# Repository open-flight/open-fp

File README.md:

# open-fp

Open source force plates for golf performance.

Two low-profile golf force plates, one per foot. Each plate has four load cells, eight in total. A single Arduino UNO Q reads them, and a web dashboard on the LAN shows live weight shift and swing replay.

> **Status:** Hardware bring-up is under way. Four of the eight load cells read on one SPI bus through the toe stripboard carrier, at about 944 Hz each (`bench/ads1220_all`; results in [`docs/VERIFIED.md`](docs/VERIFIED.md)). An assembled, no-solder ADC board for all eight channels has been designed and ordered ([`hardware/pcb/adc-board`](hardware/pcb/adc-board/README.md)). The pure-Python processing (`app/python/open_fp/`: protocol, clock, pipeline, calibration, swing detection, storage) is written and tested, and runs under `pytest` with no hardware. The web UI and a desktop simulator work too: run `python tools/sim/sim_server.py` and open http://localhost:7070 to see live weight shift, swing capture, replay and diagnostics on synthetic swings. **Not written yet:** the production MCU firmware (`app/sketch/`) and the board-side `main.py` that links it to the pipeline. Milestones: [`docs/PROJECT_INIT.md` §12](docs/PROJECT_INIT.md#12-milestones-and-acceptance-checks) (M0–M1 done, M2 in progress).

## What it measures

| Output | Notes |
|---|---|
| Vertical force per foot (Fz) | N and %BW |
| Centre of pressure (CoP) per foot and combined | mm, in the stance frame |
| Lead/trail weight % | set by handedness (RH/LH) |
| Swing capture and metrics | address, max trail, transition, max lead, finish |

## Limitations

- **Vertical force only.** Each plate has four vertical cells, which give Fz and CoP (x, y) per plate. The plates cannot measure shear (horizontal) forces or torque about the vertical axis, so the app does not report ground torque or horizontal force.
- **Inter-channel skew up to ~1 ms.** Each ADC runs on its own oscillator. All eight are read on the DRDY signal of one board.
- **200 Hz stream.** The MCU↔Linux router link runs at 115200 baud. That is enough for weight shift but too slow for impact transients.
- **Temperature drift.** Half-bridge cells and their completion resistors drift with temperature. The app auto-zeros when the plates are empty.
- **Impact timing is external.** Impact is known only when the OpenFlight launch monitor sends a shot event or you mark it by hand. Over Wi-Fi with NTP, expect 5–20 ms of error.

## Hardware

- 2 × 12" × 12" × 1/4" 6061 aluminum plates, 8 × 50 kg half-bridge load cells, 8 × ADS1220 24-bit ADCs, 1 × Arduino UNO Q
- Bill of materials: [`hardware/bom.md`](hardware/bom.md) (its Buy column uses Amazon affiliate links)
- ADC wiring: hand-built stripboard carriers ([`docs/harness.md`](docs/harness.md)), or the assembled, no-solder ADC board in [`hardware/pcb/adc-board/`](hardware/pcb/adc-board/README.md)
- Print files: [`hardware/cad/`](hardware/cad/) (STL, STEP, and the CadQuery sources)
- Assembly: [`docs/assembly.md`](docs/assembly.md) · Wiring: [`docs/wiring.md`](docs/wiring.md) · System wiring, step by step: [`docs/harness.md`](docs/harness.md) · One-cell bench test: [`docs/bench-single-cell.md`](docs/bench-single-cell.md) · Calibration: [`docs/calibration.md`](docs/calibration.md)

## Repository layout

```
app/        Arduino App Lab app: MCU sketch, Python processing, static web UI
bench/      bring-up sketches for the ADS1220s
docs/       project spec, assembly, wiring, calibration, VERIFIED log
hardware/   BOM and CAD (STL/STEP in Git LFS)
tools/      deploy scripts, desktop simulator, offline analysis
tests/      pytest suite, runs without hardware
```

## Setup

Full walkthrough from a fresh clone and an unboxed board: **[`docs/SETUP.md`](docs/SETUP.md)**. The short version:

```bash
tools/dev_setup.sh          # dev machine: git-lfs, arduino-cli + UNO Q core, CAD files, .venv
# App Lab: first-boot the board as "open-fp", then create app "open-fp" with the WebUI - HTML brick
tools/board_setup.sh        # install your SSH key on the board
tools/deploy.sh             # push app/ and restart; UI at http://open-fp.local:7000
tools/logs.sh               # follow the app's Python logs
```

## Contributing

Build reports, fixes and new features are welcome. Start with [`CONTRIBUTING.md`](CONTRIBUTING.md): it covers the dev setup (no hardware needed), the checks CI runs, and how hardware changes are recorded. Please follow the [Code of Conduct](CODE_OF_CONDUCT.md), and report security issues privately as described in [`SECURITY.md`](SECURITY.md).

## License

[AGPL-3.0](LICENSE), the same license as [OpenFlight](https://github.com/open-flight/openflight).

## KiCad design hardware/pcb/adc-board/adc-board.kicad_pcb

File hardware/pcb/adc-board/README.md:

# ADC board (8 × ADS1220, UNO Q shield)

One assembled PCB that replaces the two stripboard ADC carriers, the eight ADS1220 breakouts, the bridge resistors and the whole wire harness. It plugs straight onto the UNO Q like any UNO shield. Each load-cell cable plugs into its own JST-XH socket. PCBWay assembles every part, so you don't solder anything.

**Rev B** (this revision) is the same circuit as rev A in a shorter board: 204.5 mm instead of 284 mm, with an OpenFlight logo on the top silkscreen. The parts, nets, pin map and each channel's layout are unchanged; only where the channels sit along the board moved. Rev A was built and passed bring-up (all 8 ADCs read back, supply and reference checked) on 2026-11-09. The enclosure in `hardware/cad` is now rev B to match (see below).

**Firmware doesn't change.** The pin map and the ADC configuration (`0E C4 40 00`: AIN0−AIN1, gain 128, PGA on, 1 kSPS turbo, continuous, external reference REFP0/REFN0) are the same as on the stripboard build.

| | |
|---|---|
| Board | 204.5 × 50 mm (54.7 mm at the header tabs), 2 layers, 1.6 mm FR4, 1 oz |
| Parts | 8 × ADS1220IPWR (on the board itself, not modules), 8 × JST-XH 3-pin side-entry SMT, 4 SMD shield headers, 0603/0805 passives. **All on the underside.** The top has copper and silkscreen only |
| Renders | [`renders/`](renders): top, bottom, 3D |
| Schematic | [`adc-board-schematic.pdf`](adc-board-schematic.pdf) |
| Order files | [`adc-board-gerbers.zip`](adc-board-gerbers.zip), [`assembly/adc-board-bom.csv`](assembly/adc-board-bom.csv), [`assembly/adc-board-centroid.csv`](assembly/adc-board-centroid.csv) |
| Checks | ERC 0 errors 0 warnings; DRC 0 errors **and 0 warnings**, 0 unconnected, schematic parity clean (`kicad-cli`, KiCad 10.0.4). Against rev A: same 115 footprints, every pad on the same net, every channel's parts at the same offsets and rotations from its JST, shield headers at the same UNO Q positions, BOM byte-identical, 16 keepouts. Gerbers re-read: outline 204.50 × 54.70 mm, 187 plated and 4 mounting holes |

## Circuit (one channel; there are eight)

The same circuit as the proven breakout build, with the chip on the board:

- **ADS1220IPWR** (TSSOP-16). AVDD and DVDD go to 3V3, AVSS and DGND to GND. A 100 nF X7R sits at each supply pin, plus 10 µF per channel.
- **Ratiometric reference:** REFP0 goes to 3V3 (the same rail as the cell's E+) and REFN0 to GND, with 100 nF across them at the pins.
- **CLK** goes to GND (internal oscillator). AIN2 and AIN3 are not connected.
- **AIN0 = cell S.** **AIN1** is the midpoint of a 1.5 kΩ / 1.5 kΩ divider (Susumu RG1608P, 0.1 %, 25 ppm/°C thin film, 0603). The two resistors sit side by side next to their ADC, so they share its temperature. AIN1 is about 1.65 V, the same as the stripboard's 1 kΩ pair. Each channel draws about 3.3 mA in total (cell 1.65 mA, divider 1.1 mA, ADC ~0.4 mA), so the whole board draws about 30 mA from the Q's 3V3 pin.
- **Input RC filter (new):** 100 Ω in series with AIN0 and AIN1, 10 nF C0G across them, 1 nF C0G from each to GND. That's a differential corner of about 76 kHz and a common-mode corner of about 1.6 MHz. It keeps RF and SPI edges out of the PGA without touching the 1 kSPS signal.
- **JST-XH 3-pin** per channel. **Pin 1 = E+ (white), pin 2 = E− (black), pin 3 = S (red)**, the same order as the cradle-end JST in [`docs/wiring.md` §3–4](../../../docs/wiring.md#3-put-jst-xh-plugs-on-the-cells). The silkscreen shows the channel name, pin 1 and W/B/R next to every socket, on both sides.
- **Shared SPI.** SCLK, DIN and DOUT/DRDY go to all eight chips; SCLK has a 33 Ω series resistor at the Q. Only **L1's DRDY pin goes to D2**. The other seven DRDY pins are left unconnected (they are push-pull outputs and must never be joined). DOUT goes high-Z while CS is high, so all eight share MISO.
- **3V3 entry:** 10 µF + 100 nF next to the header's 3V3 pin. There's no power LED.

### UNO Q pin map (unchanged)

| Q pin | Net | | Q pin | Net |
|---|---|---|---|---|
| D3 | CS L1 | | D13 | SCLK (via R1 33 Ω) |
| D4 | CS L2 | | D11 | MOSI → DIN |
| D5 | CS L3 | | D12 | MISO ← DOUT |
| D6 | CS L4 | | D2 | DRDY of L1 only |
| D7 | CS R1 | | 3V3 | 3V3 |
| D8 | CS R2 | | GND | GND (three header pins) |
| D9 | CS R3 | | D0, D1, D10 | **not connected** |
| A2 | CS R4 | | everything else | not connected (pins are still fitted, for strength) |

## Layout

- All four shield headers are fitted (1×10, 2× 1×8, 1×6), at the UNO R3 positions (including the 0.16" offset between D7 and D8). The generator checks every pin against the UNO R3 grid.
- Each end's two channel blocks are packed together: the toe pair starts 7 mm past the shield headers and the heel pair 5.5 mm past them, over the header-free end of the Q (that gap is where the bus leaves the headers; tighter than this, the board will not route) (our lowest underside part, the JST at z 13.9, clears the Q's tallest, the USB-C at z 12.5). The inner channel keeps an 11 mm strip for its plug. The outer channel's plug overhangs the board end.
- Each channel sits beside its wall slot. From the board centre outwards: the ADC, then the RC network and divider, then the JST, whose mouth points along the board toward the slot. The plug lies flat under the board, in a strip kept free of parts.
- SPI and the chip selects run in the middle of the board. Over each channel's analog end (AIN pair, divider, RC, JST), keepouts stop tracks on the top layer and along the board edge, so no SPI line runs over or past AIN0/AIN1. The top layer there is solid ground.
- GND pours on both layers, stitched with about 195 vias. The Gerbers were re-read and rasterized with pygerber 2.4 as a check (rev A outline 284.0 × 54.7 mm, both copper layers).
- Rules: 0.2 mm tracks and clearance (0.4 mm for power). The only exception is tracks entering the ADS1220's 0.65 mm-pitch pins, which may come within 0.15 mm (`adc-board.kicad_dru`). Vias are 0.6/0.3 mm. Copper stays ≥ 0.3 mm from the edge.

## Channel → connector → slot

Slot x positions are in the enclosure frame (+x = toe). The JST mouth is where the plug goes in. The plug body then runs about 10 mm further, and the cable turns to its wall slot 15 mm past the mouth (**VERIFY** with a real plug).

| Ch | Ref | CS | Plate corner | Wall | Slot x | ADC at x | JST mouth at x |
|---|---|---|---|---|---|---|---|
| L1 | J1, U1 | D3 | toe, outer | +y | +124 | +87 | +109, facing +x |
| L2 | J2, U2 | D4 | toe, inner | +y | +83 | +46 | +68, facing +x |
| L3 | J3, U3 | D5 | heel, inner | +y | −67.5 | −30.5 | −52.5, facing −x |
| L4 | J4, U4 | D6 | heel, outer | +y | −108.5 | −71.5 | −93.5, facing −x |
| R1 | J5, U5 | D7 | toe, inner | −y | +83 | +46 | +68, facing +x |
| R2 | J6, U6 | D8 | toe, outer | −y | +124 | +87 | +109, facing +x |
| R3 | J7, U7 | D9 | heel, outer | −y | −108.5 | −71.5 | −93.5, facing −x |
| R4 | J8, U8 | A2 | heel, inner | −y | −67.5 | −30.5 | −52.5, facing −x |

Each JST is centred 17.8 mm from the board's centreline, on the same side as its wall.

## Stack-up (enclosure frame, z in mm)

The board sits on the Q's headers, so its height is set by the Q. Nothing fits under the current lid, so the enclosure has to grow by 2.4 mm. That's within the 2.6 mm the ramps allow.

| z | What |
|---|---|
| 0 | base underside |
| 2.4 | floor top |
| 5.4 | ADC pad tops (standoffs start here) |
| 7.4 – 9.0 | UNO Q PCB (on its 5 mm bosses) |
| ~12.5 | tallest Q top-side parts (USB-C) |
| 17.5 | top of the Q's female headers (8.5 mm; **VERIFY**) |
| 17.5 – 20.0 | our SMD male headers' plastic body (2.54 mm); posts go down into the Q's headers |
| **20.0 – 21.6** | **this board** |
| ~13.9 – 20.0 | underside parts: JST-XH side-entry (~6.1 mm high, **VERIFY**) and the plug beside it; the TSSOP and passives reach only 18.8 – 20.0 |
| 21.6 | board top: copper and silkscreen only, no parts, no through-hole pins |
| 22.3 | lid underside **after the change below** (0.7 mm air gap) |
| 24.3 | lid top after the change (ceiling 24.5) |

Support: four M2.5 holes on the centreline at x −90, −58.5, +74 and +105.5 (the inner two in the inner plugs' part-free strips). The enclosure has a pad and insert under each (rev B changes below). Use standoffs **14.5 mm long** (board underside 20.0 − pad top 5.4 = 14.6). Male-female hex standoffs work if the male thread fits the 2.5 mm-deep insert; otherwise use F-F standoffs with a short M2.5 set screw (**VERIFY** the insert depth). There's no room for screw heads on top (0.7 mm gap), so the standoffs only carry the board. The 32 header pins hold it down, and the lid stops it lifting more than 0.7 mm. If you want it clamped, stick a 0.5–0.7 mm rubber or foam dot on the board top over each standoff.

The USB-C cable to the Q runs along the floor/pads under the board (z 5.4 – ~10). Route it beside the two heel standoffs at y = 0. Nothing else under the board comes below z ≈ 13.9.

## Rev B enclosure changes (applied 2026-11-11, see `docs/VERIFIED.md`)

The enclosure is now generated from [`hardware/cad/src/centre_enclosure.py`](../../cad/src/centre_enclosure.py) (`REV_B`); the rev A changes below still apply. On top of them, for the shorter board:

1. **Cable slots** at x −108.5, −67.5, +83 and +124, in both long walls (same 6 mm width, z 2.4 … 19.0).
2. **Standoff pads** (Ø9, top z 5.4) with an M2.5 insert hole (Ø3.5 × 2.5 mm) under each board hole: (−90, 0), (−58.5, 0), (+74, 0) and (+105.5, 0). The two 90 × 50 mm pads and their 7.5 mm insert grid are gone. **Install 4 ADC inserts.**
3. **Lid posts** at x −117.5 and +133, y ±23: 2 mm past the outer slots' edges, so the outer cables turn to their slots clear of them. Still 5 mm in from the end and long walls, as in rev A.
4. **Shorter:** the cavity is x −122.5 … +138 (was ±145), so the outside is **265.3 × 60.8 mm** (was 294.8; width and height unchanged) and spans x −124.9 … +140.4, no longer centred on x = 0. The ~x −106 … +122 first estimated here is too short: the outer slots alone reach x −111.5 and +127, and the lid posts have to sit past them. A shorter box would need the lid posts beside the board ends on the centreline (|y| < 9, between the plugs), which would block the USB-C cable at the heel.
5. Unchanged: UNO Q bosses, the USB-C slot (heel end wall, y ±7, z 6.4 … 14.4, now 88 mm from the Q's edge instead of 111), the rev A wall raise and lid lip cut, the lid's vents on the same 12 mm grid (x −96 … +108 now).

Checked with [`hardware/cad/src/check_adc_fit.py`](../../cad/src/check_adc_fit.py), which reads the board outline and holes from `adc-board.kicad_pcb`: all four holes land on pad inserts, and the board, the underside-part zone (z 13.9 – 20), the UNO Q stack, the standoffs, all eight plugs (10 × 10 mm past each JST mouth) and 4 mm cable runs from each plug to its slot clear the base and the fitted lid (0.00 mm³ overlap). Overlay: [`hardware/cad/renders/centre-enclosure-adc-fit.png`](../../cad/renders/centre-enclosure-adc-fit.png). Rev A's [stripboard carriers](../../../docs/harness.md) don't fit rev B (no pad grid); `centre_enclosure.py --rev a` regenerates the rev A enclosure for them.

## Rev A enclosure changes (applied to the STEP/STL on 2026-10-12, see `docs/VERIFIED.md`)

1. **Raise the base walls by 2.4 mm:** wall top z 19.9 → **22.3**. Lid posts (±140, ±23) grow by the same amount, so the M2.5 inserts stay at the top. The lid plate stays 2.0 mm thick, so the outer height goes 21.9 → **24.3** (ramps rise 24.5). The Q bosses, ADC pads and inserts stay as they are.
2. **Cut the lid's locating lip away along both long sides for x −20 … +34** (applied as x −34 … +34, so the lid fits either way round). The board has tabs out to y ±27.35 under the shield headers (x −18 … +32). The SMD header pads need them, because the Q's headers sit only 2.5 mm from its edge. Elsewhere the board stays inside y ±25.0, clear of the lip ring (inner edge ±25.3). After the raise, the lip spans z 20.8 – 22.3 and would hit the tabs (board top 21.6).
3. **Make the eight cable slots taller:** z 2.4 … 9.4 → **z 2.4 … 19.0**, same 6 mm width, at x ±85 and ±125 in both long walls. The plug and cable leave the JST at about z 15 – 18 (just under the board), 7 mm in from the wall, so a tall slot lets the cable run straight out instead of kinking down to the floor. If you'd rather keep the slots, the cable needs an S-bend of about 8 mm in the last 10 mm (**VERIFY** with a real plug).
4. Rev A only: board corner notches (x beyond ±135.5, |y| beyond 18.5) cleared the lid posts. Rev B has no notches.

## What changes for you, compared with the stripboard build

- **Nothing in the firmware or config.** Same pins, same registers, same channel order. `signs` in the config still covers E+/E− swaps.
- **No soldering.** At each cable's board end, crimp a 3-way **JST XHP-3** housing (pin 1 white E+, 2 black E−, 3 red S), the same pinout as the cradle end, then thread the cable through its slot. Plug it in before you lower the board onto the Q (the plugs go in sideways, under the board).
- The cable **shield/drain** has no pin on the 3-way XH. Cut it back and insulate it at both ends. If noise turns out worse than on the stripboard, ground the drain at the board end under a standoff screw (**VERIFY** on the bench).
- The bridge resistors are 1.5 kΩ instead of 1 kΩ (same 0.1 % class, now 25 ppm/°C thin film). AIN1 sits at the same ~1.65 V, so the calibration procedure is the same. Recalibrate anyway, as with any new hardware.
- No breakout modules, no headers to solder, no harness, no strip cuts. The bring-up checks in `docs/harness.md` §4–5 still apply. The `bench/spi_diag` sketch and `tools/bench/multi_cell.py` work unchanged.

## Ordering at PCBWay

**PCB:** 2 layers, 204.5 × 54.7 mm, FR-4 TG150, 1.6 mm, 1 oz outer copper, min track/space 6/6 mil (0.15 mm), min hole 0.3 mm, lead-free HASL (or ENIG for a flatter TSSOP land, about +$10), green mask, white silk, quantity **5**. Upload `adc-board-gerbers.zip` (Gerber X2 + separate PTH/NPTH Excellon, origin at the board's lower-left corner).

**Assembly:** turnkey, quantity **2** (or 3), **single side: bottom** (every part is on the bottom; there are no through-hole parts). Upload `assembly/adc-board-bom.csv` and `assembly/adc-board-centroid.csv`. In the notes:

- "All components on the bottom side. Centroid file is KiCad's, viewed from the top. Please send the placement review (DFM) before production."
- "Shield headers J9–J12: XKB X6511WVS-xxH-C60D48**R2** (pin 1 pad on the left), the same parts as order T-2Y12W1042560A. Not the R1 type. Please confirm in the DFM placement review."
- "U1–U8 pin 1: dot on silkscreen/fab. J1–J8: JST S3B-XH-SM4-TB(LF)(SN), mouth facing the board end."

Actual rev A cost (PCBWay order T-2Y12W1042560A, October 2026, 2 assembled boards): parts $70.20, assembly $29.00, PCBs $40.50, so $139.70 before shipping. Lead time was 16–18 days once the headers were swapped. With freight, bank fee, duty and the DHL duties-paid fee it came to $234.10 delivered to the US (duty and tax were $62.31). Rev B's board is about 28 % smaller, so the PCB line should come down a little.

### BOM (12 lines; the full file is `assembly/adc-board-bom.csv`)

| Refs | Qty | Part | MPN |
|---|---|---|---|
| U1–U8 | 8 | ADC, TSSOP-16 | TI ADS1220IPWR |
| R101, R102, … R801, R802 | 16 | 1.5 kΩ 0.1 % 25 ppm 0603 | Susumu RG1608P-152-B-T5 (alt. Panasonic ERA-3AEB152V) |
| R103, R104, … | 16 | 100 Ω 1 % 0603 | Yageo RC0603FR-07100RL |
| R1 | 1 | 33 Ω 1 % 0603 | Yageo RC0603FR-0733RL |
| C?01–C?03, C2 | 25 | 100 nF X7R 50 V 0603 | Murata GRM188R71H104KA93D |
| C?04 | 8 | 10 nF C0G 50 V 0603 | Murata GRM1885C1H103JA01D |
| C?05, C?06 | 16 | 1 nF C0G 50 V 0603 | Murata GRM1885C1H102JA01D |
| C?07, C1 | 9 | 10 µF X5R 16 V 0805 | Murata GRM21BR61C106KE15L |
| J1–J8 | 8 | JST-XH 3-pin side-entry SMT | JST S3B-XH-SM4-TB(LF)(SN) |
| J12 | 1 | 1×10 SMT male header, pin 1 pad left | XKB X6511WVS-10H-C60D48R2 (alt. Samtec TSM-110-01-T-SV-P) |
| J9, J11 | 2 | 1×8 SMT male header, pin 1 pad left | XKB X6511WVS-08H-C60D48R2 (alt. Samtec TSM-108-01-T-SV-P) |
| J10 | 1 | 1×6 SMT male header, pin 1 pad left | XKB X6511WVS-06H-C60D48R2 (alt. Samtec TSM-106-01-T-SV-P) |

The headers were Samtec TSM on the first quote. PCBWay had no stock (26–28 day lead time) and fitted the XKB **R2** parts instead, which rev A was built with and passed bring-up on. R2 has pin 1's pad on the left, matching the `Pin1Left` footprint; R1 is the mirror image and would be wrong.

Mating parts you need (not on the board): 8 × JST XHP-3 housings + 24 × SXH-001T-P0.6 crimp terminals (in the XH kit you already have).

## Regenerating

Everything is generated from [`scripts/design.py`](scripts/design.py), which holds the parts, nets and MPNs. The `.kicad_pro`, `.kicad_sch` and `.kicad_pcb` open and edit as a normal KiCad 10 project. If you edit by hand, don't rerun the generators.

```sh
# KiCad 10 (macOS paths are the defaults; override KICAD_CLI / KPY), Java 21+, Freerouting 2.4.1
hardware/pcb/adc-board/scripts/build.sh /path/to/freerouting.jar   # sch, ERC, netlist check, place, route, DRC
hardware/pcb/adc-board/scripts/export.sh                           # gerbers, drill, zip, BOM, centroid, renders, PDF
```

`build.sh` reruns Freerouting until DRC reports zero errors. Use **Freerouting 2.4.1**: on rev B it routes clean on the first try, while 2.2.4 and 2.5.0 leave a few connections unrouted every time (for a given board and settings Freerouting gives the same result, so retries don't help). `FREEROUTING_ARGS` passes extra router options through `scripts/route.py`.

The logo comes from `art/openflight-logo.png` via `scripts/make_logo.py` (needs Pillow), which writes `art/openflight-logo.runs` for `gen_pcb.py`. It is drawn in 0.16 mm pixels, so no printed feature is thinner than PCBWay's 0.15 mm silkscreen minimum.

## VERIFY before ordering / on arrival

1. **UNO Q female header height.** This assumes 8.5 mm (tops at z 17.5). Measure it. Every z above depends on it.
2. **Shield headers:** confirmed on rev A. The XKB X6511WVS-…-C60D48R2 parts fit the `PinHeader_1x..._Vertical_SMD_Pin1Left` footprint and mate with the UNO Q. If PCBWay proposes another substitute, it must have pin 1's pad on the left, a 2.54 mm body and posts ≥ 5.8 mm.
3. **JST S3B-XH-SM4-TB:** mouth on the side away from the signal pads (toward the MP tabs), body height ~6 mm, and how far the mated XHP-3 plug and its crimps stick out (~10 mm assumed). KiCad has no 3D model for this part, so the renders don't show it.
4. **Cable route from plug to slot.** Do it with a real plug and cable. The slots are already tall (rev A change 3).
5. **Noise, chip-on-board vs breakout module.** It should be equal or better: same die, decoupling at the pins, plus an RC filter. Confirm with `tools/bench/single_cell.py` and the 4-cell live view before calibrating.
6. **Standoff length** (14.5 mm) and the insert depth (2.5 mm).
7. **Lid fit:** 0.7 mm between the board top and the raised lid. The board has no top-side parts and no through-hole pins, but check the board isn't bowed.
8. **Shield drain** left unconnected (see above).

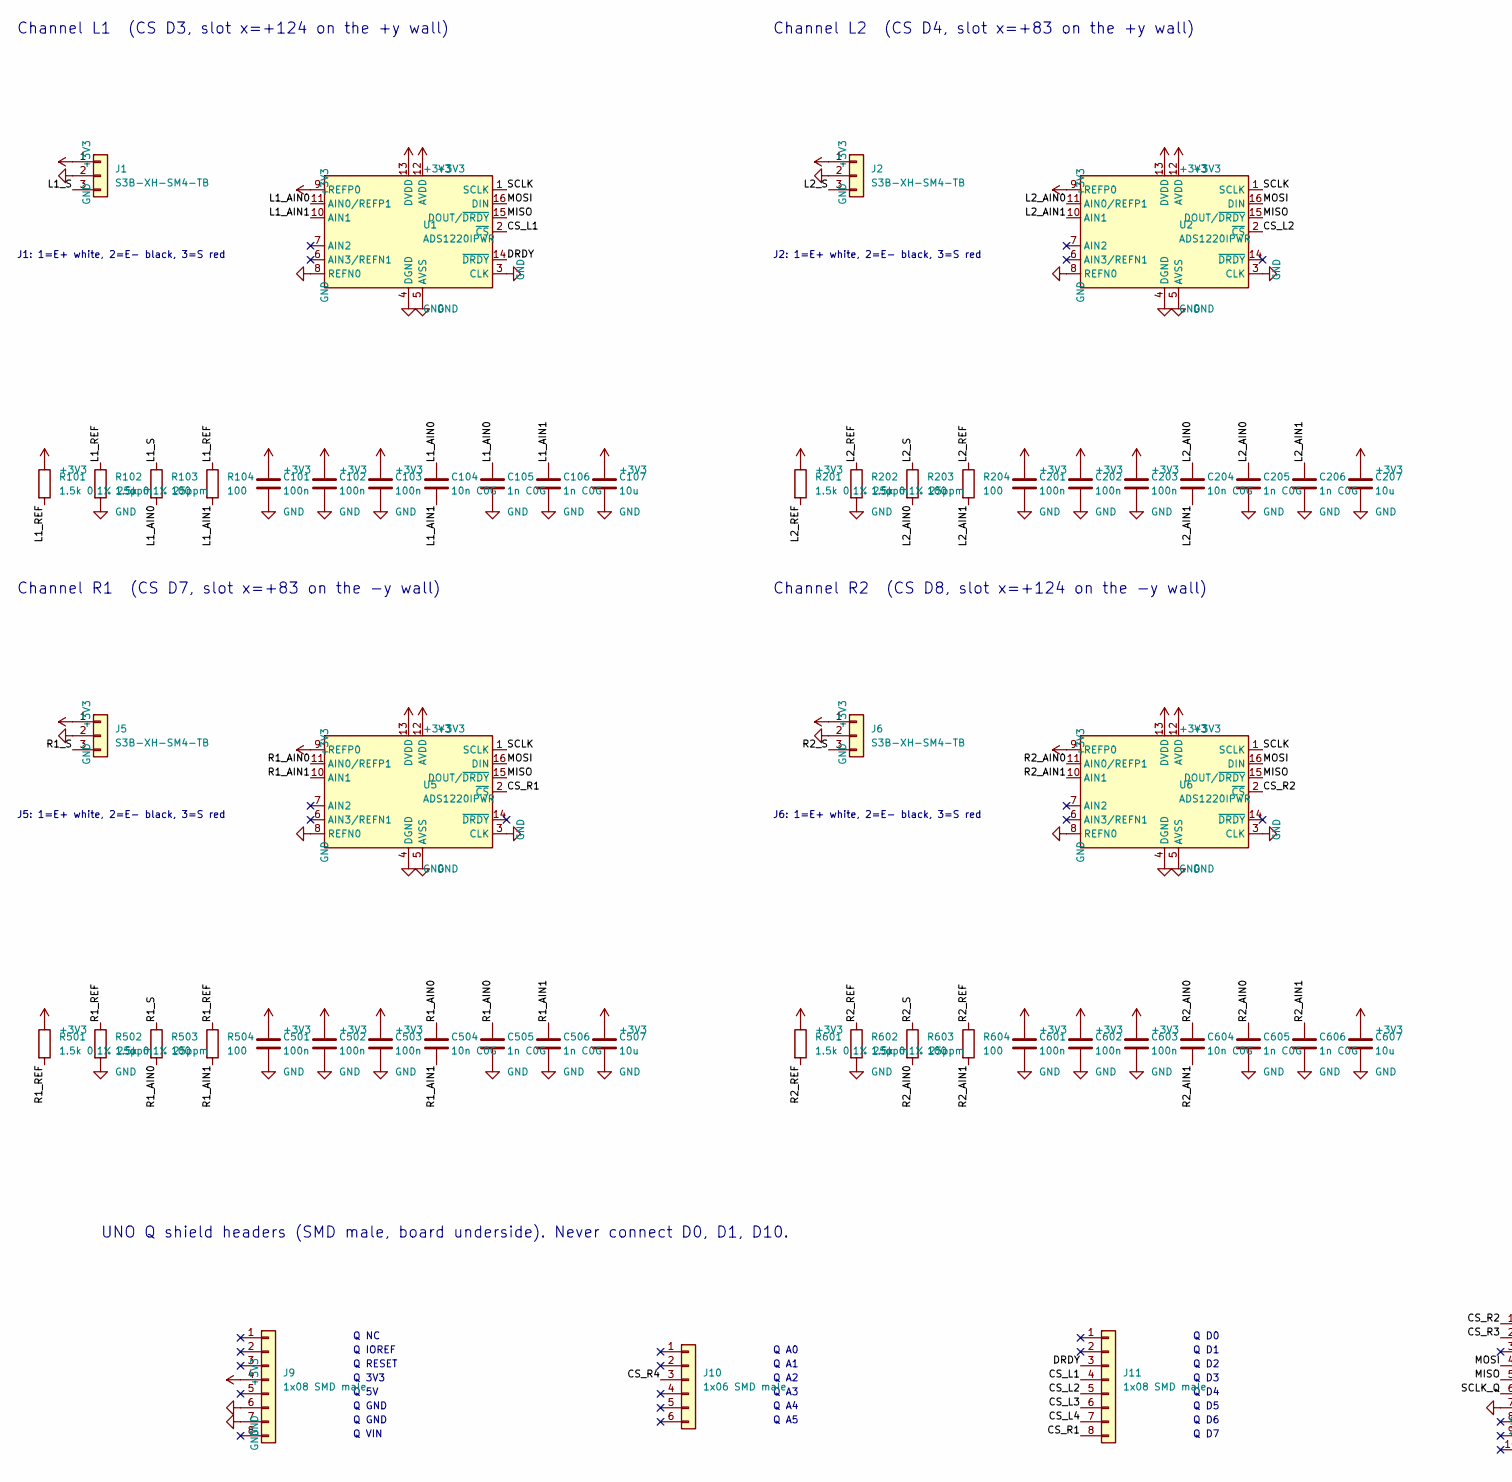
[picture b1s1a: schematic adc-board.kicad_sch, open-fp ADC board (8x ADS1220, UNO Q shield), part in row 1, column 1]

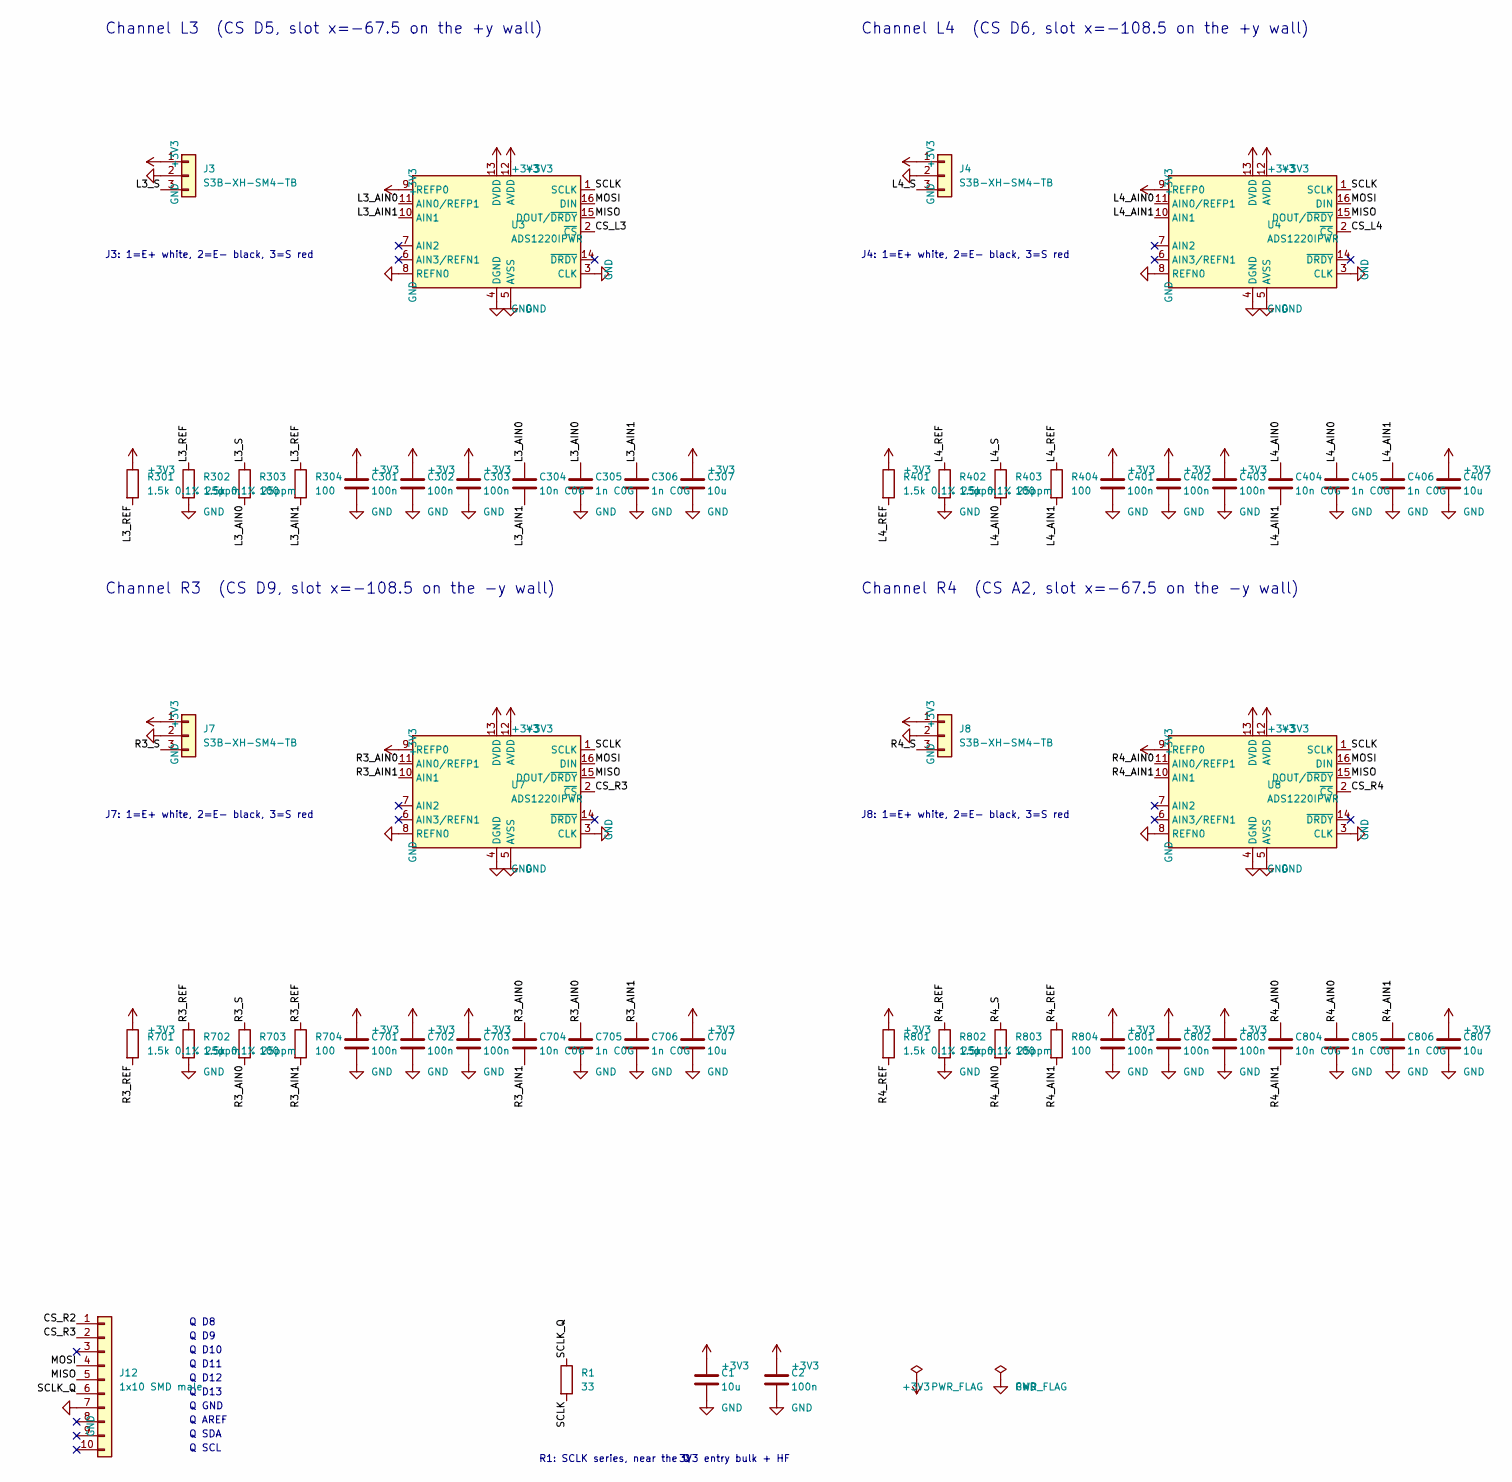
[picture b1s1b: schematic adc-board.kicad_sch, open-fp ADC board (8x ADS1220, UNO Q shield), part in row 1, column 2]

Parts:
C1, C107, C207, C307, C407, C507, C607, C707, C807: 10u; C_0805_2012Metric; MPN GRM21BR61C106KE15L
C2, C101, C102, C103, C201, C202, C203, C301, C302, C303, C401, C402, C403, C501, C502, C503, C601, C602, C603, C701, C702, C703, C801, C802, C803: 100n; C_0603_1608Metric; MPN GRM188R71H104KA93D
C104, C204, C304, C404, C504, C604, C704, C804: 10n C0G; C_0603_1608Metric; MPN GRM1885C1H103JA01D
C105, C106, C205, C206, C305, C306, C405, C406, C505, C506, C605, C606, C705, C706, C805, C806: 1n C0G; C_0603_1608Metric; MPN GRM1885C1H102JA01D
J1, J2, J3, J4, J5, J6, J7, J8: S3B-XH-SM4-TB; JST_XH_S3B-XH-SM4-TB_1x03-1MP_P2.50mm_Horizontal; MPN S3B-XH-SM4-TB(LF)(SN)
J9, J11: 1x08 SMD male; PinHeader_1x08_P2.54mm_Vertical_SMD_Pin1Left; MPN TSM-108-01-T-SV-P
J10: 1x06 SMD male; PinHeader_1x06_P2.54mm_Vertical_SMD_Pin1Left; MPN TSM-106-01-T-SV-P
J12: 1x10 SMD male; PinHeader_1x10_P2.54mm_Vertical_SMD_Pin1Left; MPN TSM-110-01-T-SV-P
R1: 33; R_0603_1608Metric; MPN RC0603FR-0733RL
R101, R102, R201, R202, R301, R302, R401, R402, R501, R502, R601, R602, R701, R702, R801, R802: 1.5k 0.1% 25ppm; R_0603_1608Metric; MPN RG1608P-152-B-T5
R103, R104, R203, R204, R303, R304, R403, R404, R503, R504, R603, R604, R703, R704, R803, R804: 100; R_0603_1608Metric; MPN RC0603FR-07100RL
U1, U2, U3, U4, U5, U6, U7, U8: ADS1220IPWR; TSSOP-16_4.4x5mm_P0.65mm; MPN ADS1220IPWR

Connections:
+3V3: C1.1, C2.1, C101.1, C102.1, C103.1, C107.1, C201.1, C202.1, C203.1, C207.1, C301.1, C302.1, C303.1, C307.1, C401.1, C402.1, C403.1, C407.1, C501.1, C502.1, C503.1, C507.1, C601.1, C602.1, C603.1, C607.1, C701.1, C702.1, C703.1, C707.1, C801.1, C802.1, C803.1, C807.1, J1.1, J2.1, J3.1, J4.1, J5.1, J6.1, J7.1, J8.1, J9.4, R101.1, R201.1, R301.1, R401.1, R501.1, R601.1, R701.1, R801.1, U1.9 (REFP0), U1.12 (AVDD), U1.13 (DVDD), U2.9 (REFP0), U2.12 (AVDD), U2.13 (DVDD), U3.9 (REFP0), U3.12 (AVDD), U3.13 (DVDD), U4.9 (REFP0), U4.12 (AVDD), U4.13 (DVDD), U5.9 (REFP0), U5.12 (AVDD), U5.13 (DVDD), U6.9 (REFP0), U6.12 (AVDD), U6.13 (DVDD), U7.9 (REFP0), U7.12 (AVDD), U7.13 (DVDD), U8.9 (REFP0), U8.12 (AVDD), U8.13 (DVDD)
/CS_L1: J11.4, U1.2 (~CS)
/CS_L2: J11.5, U2.2 (~CS)
/CS_L3: J11.6, U3.2 (~CS)
/CS_L4: J11.7, U4.2 (~CS)
/CS_R1: J11.8, U5.2 (~CS)
/CS_R2: J12.1, U6.2 (~CS)
/CS_R3: J12.2, U7.2 (~CS)
/CS_R4: J10.3, U8.2 (~CS)
/DRDY: J11.3, U1.14 (~DRDY)
/L1_AIN0: C104.1, C105.1, R103.2, U1.11 (AIN0/REFP1)
/L1_AIN1: C104.2, C106.1, R104.2, U1.10 (AIN1)
/L1_REF: R101.2, R102.1, R104.1
/L1_S: J1.3, R103.1
/L2_AIN0: C204.1, C205.1, R203.2, U2.11 (AIN0/REFP1)
/L2_AIN1: C204.2, C206.1, R204.2, U2.10 (AIN1)
/L2_REF: R201.2, R202.1, R204.1
/L2_S: J2.3, R203.1
/L3_AIN0: C304.1, C305.1, R303.2, U3.11 (AIN0/REFP1)
/L3_AIN1: C304.2, C306.1, R304.2, U3.10 (AIN1)
/L3_REF: R301.2, R302.1, R304.1
/L3_S: J3.3, R303.1
/L4_AIN0: C404.1, C405.1, R403.2, U4.11 (AIN0/REFP1)
/L4_AIN1: C404.2, C406.1, R404.2, U4.10 (AIN1)
/L4_REF: R401.2, R402.1, R404.1
/L4_S: J4.3, R403.1
/MISO: J12.5, U1.15 (DOUT/~DRDY), U2.15 (DOUT/~DRDY), U3.15 (DOUT/~DRDY), U4.15 (DOUT/~DRDY), U5.15 (DOUT/~DRDY), U6.15 (DOUT/~DRDY), U7.15 (DOUT/~DRDY), U8.15 (DOUT/~DRDY)
/MOSI: J12.4, U1.16 (DIN), U2.16 (DIN), U3.16 (DIN), U4.16 (DIN), U5.16 (DIN), U6.16 (DIN), U7.16 (DIN), U8.16 (DIN)
/R1_AIN0: C504.1, C505.1, R503.2, U5.11 (AIN0/REFP1)
/R1_AIN1: C504.2, C506.1, R504.2, U5.10 (AIN1)
/R1_REF: R501.2, R502.1, R504.1
/R1_S: J5.3, R503.1
/R2_AIN0: C604.1, C605.1, R603.2, U6.11 (AIN0/REFP1)
/R2_AIN1: C604.2, C606.1, R604.2, U6.10 (AIN1)
/R2_REF: R601.2, R602.1, R604.1
/R2_S: J6.3, R603.1
/R3_AIN0: C704.1, C705.1, R703.2, U7.11 (AIN0/REFP1)
/R3_AIN1: C704.2, C706.1, R704.2, U7.10 (AIN1)
/R3_REF: R701.2, R702.1, R704.1
/R3_S: J7.3, R703.1
/R4_AIN0: C804.1, C805.1, R803.2, U8.11 (AIN0/REFP1)
/R4_AIN1: C804.2, C806.1, R804.2, U8.10 (AIN1)
/R4_REF: R801.2, R802.1, R804.1
/R4_S: J8.3, R803.1
/SCLK: R1.2, U1.1 (SCLK), U2.1 (SCLK), U3.1 (SCLK), U4.1 (SCLK), U5.1 (SCLK), U6.1 (SCLK), U7.1 (SCLK), U8.1 (SCLK)
/SCLK_Q: J12.6, R1.1
GND: C1.2, C2.2, C101.2, C102.2, C103.2, C105.2, C106.2, C107.2, C201.2, C202.2, C203.2, C205.2, C206.2, C207.2, C301.2, C302.2, C303.2, C305.2, C306.2, C307.2, C401.2, C402.2, C403.2, C405.2, C406.2, C407.2, C501.2, C502.2, C503.2, C505.2, C506.2, C507.2, C601.2, C602.2, C603.2, C605.2, C606.2, C607.2, C701.2, C702.2, C703.2, C705.2, C706.2, C707.2, C801.2, C802.2, C803.2, C805.2, C806.2, C807.2, J1.2, J2.2, J3.2, J4.2, J5.2, J6.2, J7.2, J8.2, J9.6, J9.7, J12.7, R102.2, R202.2, R302.2, R402.2, R502.2, R602.2, R702.2, R802.2, U1.3 (CLK), U1.4 (DGND), U1.5 (AVSS), U1.8 (REFN0), U2.3 (CLK), U2.4 (DGND), U2.5 (AVSS), U2.8 (REFN0), U3.3 (CLK), U3.4 (DGND), U3.5 (AVSS), U3.8 (REFN0), U4.3 (CLK), U4.4 (DGND), U4.5 (AVSS), U4.8 (REFN0), U5.3 (CLK), U5.4 (DGND), U5.5 (AVSS), U5.8 (REFN0), U6.3 (CLK), U6.4 (DGND), U6.5 (AVSS), U6.8 (REFN0), U7.3 (CLK), U7.4 (DGND), U7.5 (AVSS), U7.8 (REFN0), U8.3 (CLK), U8.4 (DGND), U8.5 (AVSS), U8.8 (REFN0)

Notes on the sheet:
Channel L1 (CS D3, slot x=+124 on the +y wall)
J1: 1=E+ white, 2=E- black, 3=S red
Channel L2 (CS D4, slot x=+83 on the +y wall)
J2: 1=E+ white, 2=E- black, 3=S red
Channel L3 (CS D5, slot x=-67.5 on the +y wall)
J3: 1=E+ white, 2=E- black, 3=S red
Channel L4 (CS D6, slot x=-108.5 on the +y wall)
J4: 1=E+ white, 2=E- black, 3=S red
Channel R1 (CS D7, slot x=+83 on the -y wall)
J5: 1=E+ white, 2=E- black, 3=S red
Channel R2 (CS D8, slot x=+124 on the -y wall)
J6: 1=E+ white, 2=E- black, 3=S red
Channel R3 (CS D9, slot x=-108.5 on the -y wall)
J7: 1=E+ white, 2=E- black, 3=S red
Channel R4 (CS A2, slot x=-67.5 on the -y wall)
J8: 1=E+ white, 2=E- black, 3=S red
UNO Q shield headers (SMD male, board underside). Never connect D0, D1, D10.
Q NC
Q IOREF
Q RESET
Q 3V3
Q 5V
Q GND
Q VIN
Q A0
Q A1
Q A2
Q A3
Q A4
Q A5
Q D0
Q D1
Q D2
Q D3
Q D4
Q D5
Q D6
Q D7
Q D8
Q D9

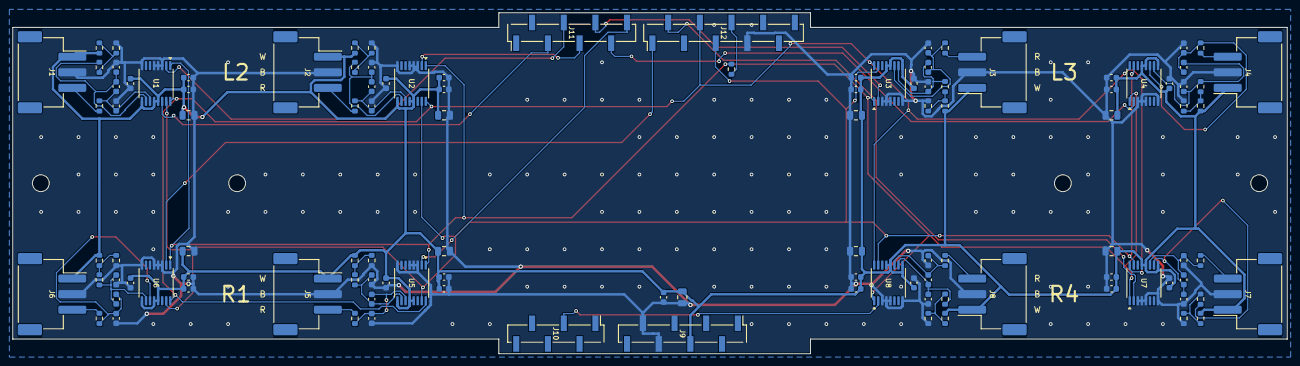
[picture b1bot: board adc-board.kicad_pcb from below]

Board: 2 copper layers, 204.5 x 54.7 mm, 115 parts (111 on the bottom side), 47 nets.

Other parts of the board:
H1, H2, H3, H4: M2.5; MountingHole_2.7mm_M2.5

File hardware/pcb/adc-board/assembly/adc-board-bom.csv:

Item,Designator,Qty,Manufacturer,MPN,Description,Value,Package,Type,Side,Alternative
1,"C2,C101,C102,C103,C201,C202,C203,C301,C302,C303,C401,C402,C403,C501,C502,C503,C601,C602,C603,C701,C702,C703,C801,C802,C803",25,Murata,GRM188R71H104KA93D,Capacitor MLCC 100 nF 50 V X7R,100n,0603,SMD,Bottom,
2,"C104,C204,C304,C404,C504,C604,C704,C804",8,Murata,GRM1885C1H103JA01D,Capacitor MLCC 10 nF 50 V C0G,10n C0G,0603,SMD,Bottom,
3,"C105,C106,C205,C206,C305,C306,C405,C406,C505,C506,C605,C606,C705,C706,C805,C806",16,Murata,GRM1885C1H102JA01D,Capacitor MLCC 1 nF 50 V C0G,1n C0G,0603,SMD,Bottom,
4,"C1,C107,C207,C307,C407,C507,C607,C707,C807",9,Murata,GRM21BR61C106KE15L,Capacitor MLCC 10 uF 16 V X5R,10u,0805,SMD,Bottom,
5,"J1,J2,J3,J4,J5,J6,J7,J8",8,JST,S3B-XH-SM4-TB(LF)(SN),JST-XH 3-pin side-entry SMT header 2.5 mm,S3B-XH-SM4-TB,SMD,SMD,Bottom,
6,"J9,J11",2,XKB Connection,X6511WVS-08H-C60D48R2,"Header 1x8 2.54 mm SMT male, pin 1 pad left (R2), pick-and-place pad",1x08 SMD male,SMD,SMD,Bottom,Samtec TSM-108-01-T-SV-P
7,J10,1,XKB Connection,X6511WVS-06H-C60D48R2,"Header 1x6 2.54 mm SMT male, pin 1 pad left (R2), pick-and-place pad",1x06 SMD male,SMD,SMD,Bottom,Samtec TSM-106-01-T-SV-P
8,J12,1,XKB Connection,X6511WVS-10H-C60D48R2,"Header 1x10 2.54 mm SMT male, pin 1 pad left (R2), pick-and-place pad",1x10 SMD male,SMD,SMD,Bottom,Samtec TSM-110-01-T-SV-P
9,R1,1,Yageo,RC0603FR-0733RL,Resistor 33 Ohm 1% 0.1 W,33,0603,SMD,Bottom,
10,"R101,R102,R201,R202,R301,R302,R401,R402,R501,R502,R601,R602,R701,R702,R801,R802",16,Susumu,RG1608P-152-B-T5,Resistor thin film 1.5 kOhm 0.1% 25 ppm/C 0.1 W,1.5k 0.1% 25ppm,0603,SMD,Bottom,Panasonic ERA-3AEB152V
11,"R103,R104,R203,R204,R303,R304,R403,R404,R503,R504,R603,R604,R703,R704,R803,R804",16,Yageo,RC0603FR-07100RL,Resistor 100 Ohm 1% 0.1 W,100,0603,SMD,Bottom,
12,"U1,U2,U3,U4,U5,U6,U7,U8",8,Texas Instruments,ADS1220IPWR,"24-bit 2 kSPS 4-ch delta-sigma ADC, PGA, SPI",ADS1220IPWR,TSSOP-16,SMD,Bottom,
